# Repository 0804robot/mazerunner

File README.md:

# mazerunner
Tech Week Maze Runner

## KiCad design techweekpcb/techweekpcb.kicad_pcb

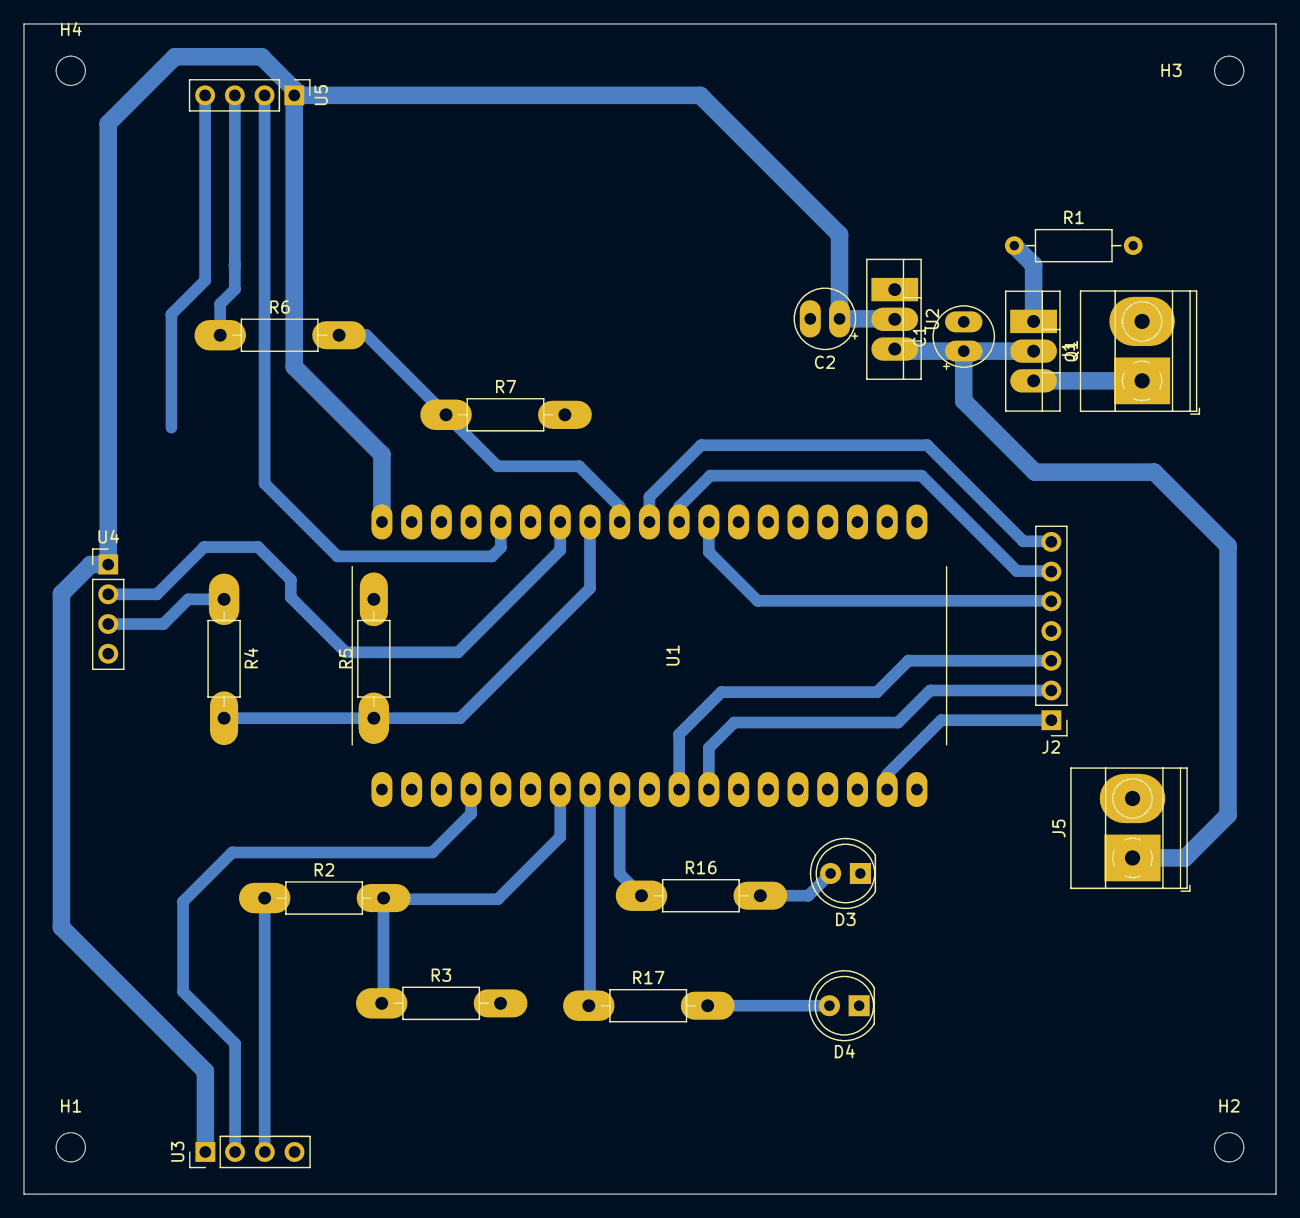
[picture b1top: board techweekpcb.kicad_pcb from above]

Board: 2 copper layers, 107.0 x 100.0 mm, 26 parts (0 on the bottom side), 24 nets.

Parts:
C1, C2: 10uF; CP_Radial_D5.0mm_P2.50mm
D3, D4: LED; LED_D5.0mm
H1, H2, H3, H4: MountingHole; MountingHole_2.5mm
J1, J5: Screw_Terminal_01x02; TerminalBlock_Phoenix_MKDS-1,5-2-5.08_1x02_P5.08mm_Horizont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
J2: Conn_01x07_Male; PinHeader_1x07_P2.54mm_Vertical
Q1: FQP27P06; TO-220-3_Vertical
R1: 1.1k; R_Axial_DIN0207_L6.3mm_D2.5mm_P10.16mm_Horizontal
R2, R4, R6: 1k; R_Axial_DIN0207_L6.3mm_D2.5mm_P10.16mm_Horizontal
R3, R5, R7: 2k; R_Axial_DIN0207_L6.3mm_D2.5mm_P10.16mm_Horizontal
R16, R17: 100; R_Axial_DIN0207_L6.3mm_D2.5mm_P10.16mm_Horizontal
U1: ESP32-S
U2: LM1084-5.0; TO-220-3_Vertical
U3, U4, U5: Ultrasonic; PinHeader_1x04_P2.54mm_Vertical

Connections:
+5V: C2.1, U1.38 (+5V), U2.2 (VO), U3.1 (VCC), U4.1 (VCC), U5.1 (VCC)
+12P: J1.1, Q1.3 (D)
+12V: C1.1, J5.1, Q1.2 (S), U2.3 (VI)
/Sensors/ECHO1: R2.1, U3.3 (ECHO)
/Sensors/ECHO2: R4.1, U4.3 (ECHO)
/Sensors/ECHO3: R6.1, U5.3 (ECHO)
EECHO1: R2.2, R3.1, U1.7 (P4)
EECHO2: R4.2, R5.1, U1.31 (P14)
EECHO3: R6.2, R7.1, U1.30 (P27)
ENA: J2.1, U1.18 (P23)
ENB: J2.7, U1.29 (P26)
ETRIG1: U1.4 (P15), U3.2 (TRIG)
ETRIG2: U1.32 (P12), U4.2 (TRIG)
ETRIG3: U1.34 (P13), U5.2 (TRIG)
GND: C1.2, C2.2, D3.1 (K), D4.1 (K), J1.2, J2.4, J5.2, R1.2, R3.2, R5.2, R7.2, U1.13 (GND), U1.19 (GND), U1.33 (GND), U2.1 (GND), U3.4 (GND), U4.4 (GND), U5.4 (GND)
IN1: J2.2, U1.12 (P19)
IN2: J2.3, U1.11 (P18)
IN3: J2.5, U1.27 (P33)
IN4: J2.6, U1.28 (P25)
unnamed: D3.2 (A), R16.2
unnamed: D4.2 (A), R17.2
unnamed: Q1.1 (G), R1.1
RLIGHT3: R16.1, U1.9 (P17)
RLIGHT4: R17.1, U1.8 (P16)

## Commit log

2022-09-25 Restructure
2022-09-25 Remove vscode and git files
2022-09-25 Boilerplate code
2022-09-25 Creating branch
2022-09-25 Fixes #10
2022-09-25 Adding function names
2022-09-25 f(Corner-Merchantry) get turn directions
2022-09-25 :sparkles: Initial Commit Resolves #1 #2
2022-09-26 Fixes #5
2022-09-26 Refactoring
2022-09-26 Add init function
2022-09-26 Turnoff motors
2022-09-26 f(corner_merchantry) name variables on declaration
2022-09-26 Refactoring code
2022-09-26 Linting
2022-09-26 PCB schematic file
2022-09-26 Adding schematic
2022-09-26 Accelerate - deccelerate
2022-09-26 Adding comments
2022-09-26 analogWrite
2022-09-28 Routing and Nerokas BOM
2022-09-28 PCB pdf file
2022-09-28 Updating schematic pdf
2022-09-30 f(main_logic) initial test
2022-09-30 f(mess) number of fixes
2022-09-30 Adding ultrasonic delsy
2022-09-30 Cleaning up code
2022-10-01 1998-felix Writing different speeds
2022-10-01 Adding
2022-10-04 Wheel rotation correction
2022-10-04 Updating BOM
